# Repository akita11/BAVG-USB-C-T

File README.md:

# BAVG-USBC-T / BAVG-USBC-T-PD / BAVG-USBC-T-PDdiv

USB TypeｰCケーブル（両側）をツイストペア線と電源線として使用して、RS485等の差動伝送を行うことができます。
複数を直列（デージーチェーン）接続することで、マルチドロップのT型トポロジ接続にできます。

[M5Stack社のRS485 Unit](https://www.switch-science.com/products/6554)や[RS485M Unit](https://github.com/akita11/RS485M_Unit)等に接続して使用できます。
USB Type-Cケーブルの、データ線(D+/D-)をデータ送信用の差動対(A/B)、電源線を給電(V/G)に用います。

このページでは以下の3種類の情報をまとめています。

## BAVG-USBC-T

両側のUSB Type-Cコネクタ間のデータ線(DP/DN)がA/B線と接続されていて、マルチドロップ型のデータ通信を行うことができます。

## BAVG-USBC-T-PD

BAVG-USBC-T-PDではUSB PD (Power Derivery)の電圧設定機能があり、給電電圧を20Vまたは12Vに設定できます。
電圧設定が有効の場合はPG (Power Good)LEDが点灯します

また2つのUSBコネクタの通信線は接続されていないため、両側のUSBコネクタでのデータ通信を行うことはできません。
2つのコネクタでデータ通信を行う場合は、PD機能のない「BAVG-USBC-T」、またはPD給電コネクタが別にある「BAVG-USBC-T-PDdiv」を使用してください。

**※USB PD電源からのUSB Type-Cケーブルは、必ず右側のUSB Type-Cコネクタ（この写真の赤丸側）へ接続してください。
（反対側に接続すると、RS485ラインのB/A端子がUSBケーブルのDP/DNに接続され、ACアダプタ等によってはQC制御によって供給電圧が変動する場合があり、高電圧の場合は機器が破損する場合があります）
またデータ通信は左側のUSB Type-Cコネクタのみに接続されています。**

通信経路と給電は以下の接続としてください。

### USB PD給電の設定

- JP1: USB PD電圧設定機能の有効無効設定
  - ショート（デフォルト） : 有効
  - オープン : =無効

- JP2でUSB PD給電電圧
  - オープン（デフォルト）: 20V
  - ショート : 12V

※USB PD電圧設定機能を有効にするのは、接続全体で1台のみとしてください。

※JP2の設定は、給電元（ACアダプタ等）へ要求する電圧で、実際に供給される電圧はUSB PD ACアダプタ等の仕様によります。
（例えば給電側の供給可能電圧が9V/15V/20Vの場合でJP2をショートした場合は9Vとなります）

## BAVG-USBC-T-PDdiv

USB Type-Cコネクタが3つあり、1つは給電用（データ線の接続なし）、残り2つは「BAVG-USBC-T」と同様にデータ線（DP/DN）が接続されており、マルチドロップ型の通信を行うことができます。

USB PDの電圧設定は「BAVG-USBC-T-PD」と同様です。

## Author

Junichi Akita (@akita11) / akita@ifdl.jp

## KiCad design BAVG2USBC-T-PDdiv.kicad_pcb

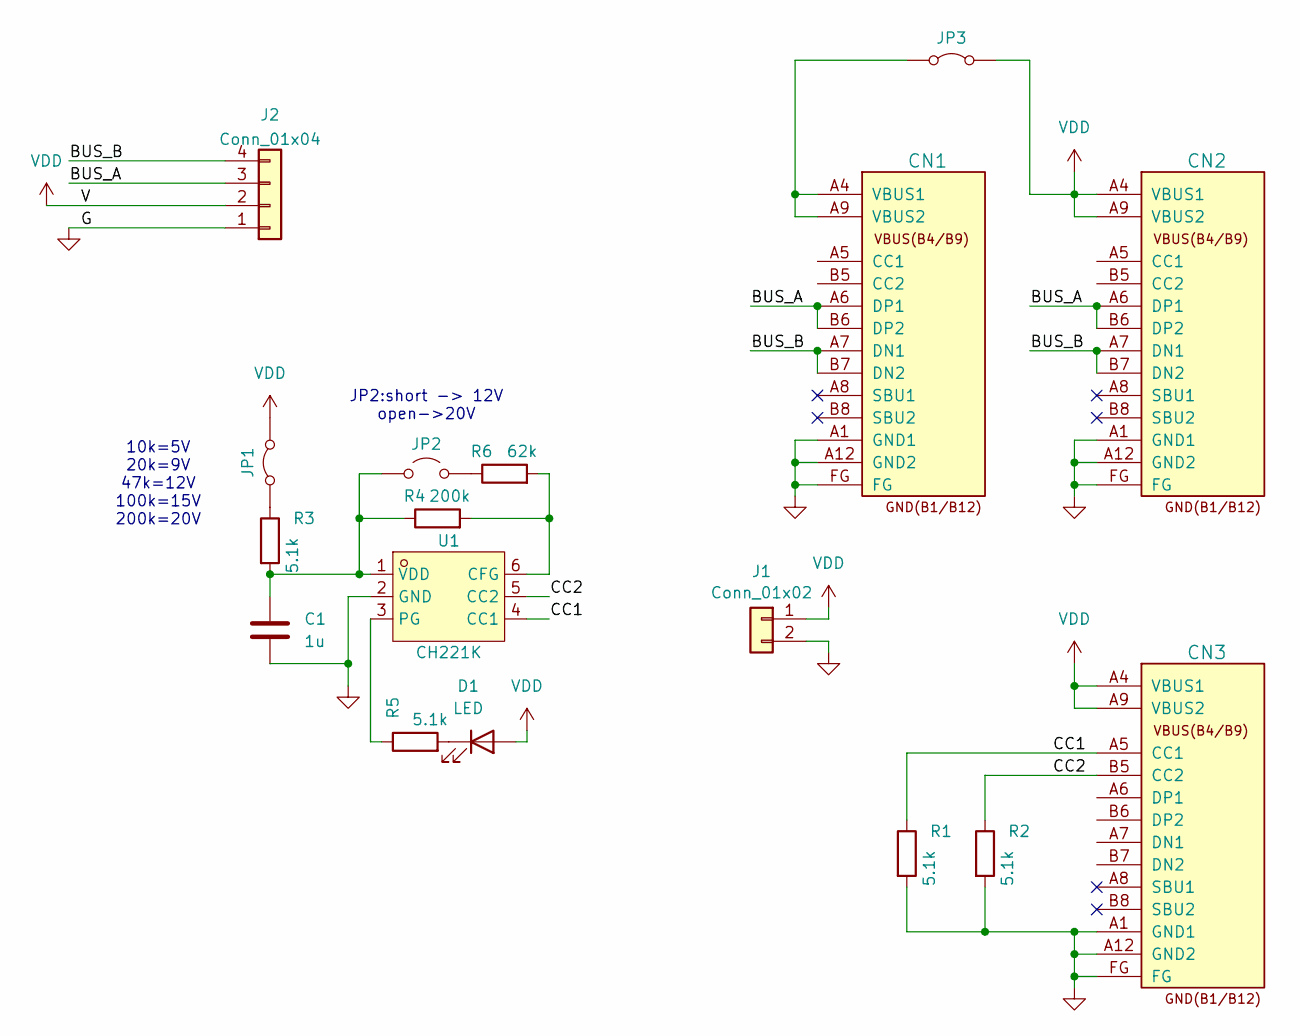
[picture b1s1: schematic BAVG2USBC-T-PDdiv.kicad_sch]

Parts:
C1: 1u; C_0603_1608Metric; LCSC C1588
CN1, CN2, CN3: CON_USB-C-16; USB-C_16P_TH; LCSC C165948
D1: LED; LED_0603_1608Metric; LCSC C2286
J1: Conn_01x02; JST_PH_B2B-PH-K_1x02_P2.00mm_Vertical
J2: Conn_01x04; CON_BAVG
JP1, JP3: Jumper_2_Bridged; SolderJumper-2_P1.3mm_Bridged_Pad1.0x1.5mm
JP2: Jumper_2_Open; SolderJumper-2_P1.3mm_Open_Pad1.0x1.5mm
R1, R2, R3, R5: 5.1k; R_0603_1608Metric; LCSC C23186
R4: 200k; R_0603_1608Metric; LCSC C25811
R6: 62k; R_0603_1608Metric; LCSC C23221
U1: CH221K; SOT-23-6_L2.9-W1.6-P0.95-LS2.8-BL-2; LCSC Part C5125736

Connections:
/BUS_A: CN1.A6 (DP1), CN1.B6 (DP2), CN2.A6 (DP1), CN2.B6 (DP2), J2.3
/BUS_B: CN1.A7 (DN1), CN1.B7 (DN2), CN2.A7 (DN1), CN2.B7 (DN2), J2.4
/CC1: CN3.A5 (CC1), R1.1, U1.4 (CC1)
/CC2: CN3.B5 (CC2), R2.1, U1.5 (CC2)
GND: C1.2, CN1.A1 (GND1), CN1.A12 (GND2), CN1.FG, CN2.A1 (GND1), CN2.A12 (GND2), CN2.FG, CN3.A1 (GND1), CN3.A12 (GND2), CN3.FG, J1.2, J2.1, R1.2, R2.2, U1.2 (GND)
unnamed: CN1.A4 (VBUS1), CN1.A9 (VBUS2), JP3.1 (A)
unnamed: D1.1 (K), R5.2
unnamed: JP1.1 (A), R3.1
unnamed: C1.1, JP2.1 (A), R3.2, R4.1, U1.1 (VDD)
unnamed: JP2.2 (B), R6.1
unnamed: R4.2, R6.2, U1.6 (CFG)
unnamed: R5.1, U1.3 (PG)
VDD: CN2.A4 (VBUS1), CN2.A9 (VBUS2), CN3.A4 (VBUS1), CN3.A9 (VBUS2), D1.2 (A), J1.1, J2.2, JP1.2 (B), JP3.2 (B)

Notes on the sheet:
10k=5V 20k=9V 47k=12V 100k=15V 200k=20V
JP2:short -> 12V open->20V

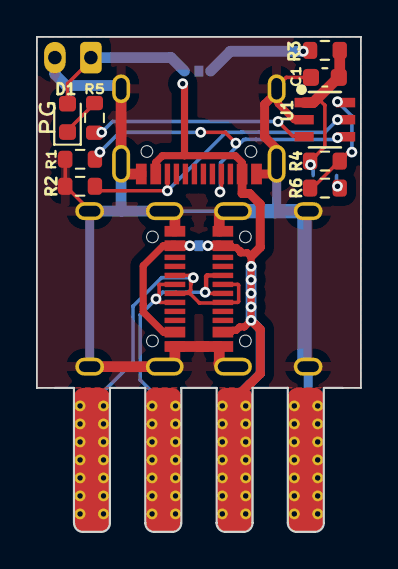
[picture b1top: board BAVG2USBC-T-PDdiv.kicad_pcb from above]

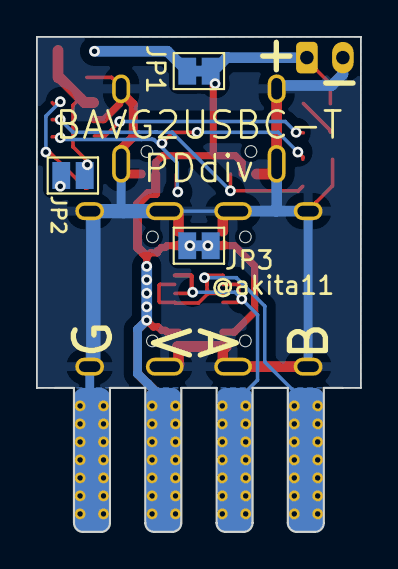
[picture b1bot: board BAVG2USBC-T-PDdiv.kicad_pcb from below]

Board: 2 copper layers, 18.0 x 27.5 mm, 17 parts (3 on the bottom side), 13 nets.

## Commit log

2026-03-17 add photo
2026-03-17 URL typo fix
2026-03-18 add PD config
2026-03-18 fix img typo
2026-05-13 add desc of PDdiv
2026-05-14 add PDdiv
2026-05-14 rename photo name
